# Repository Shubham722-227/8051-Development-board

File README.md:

# 8051 Development Board

## Introduction

Welcome to the 8051 Development Board! This README file will guide you through setting up and using our development board for your projects based on the 8051 microcontroller architecture.

## Board Overview

Our 8051 Development Board provides a platform for prototyping and developing applications using the popular 8051 microcontroller. It comes equipped with essential peripherals such as LEDs, push buttons, UART interface, ADC, and more, to facilitate rapid development.

## Features
- AT89S52 microcontroller
- 8 LEDs for visual feedback
- 4 push buttons for user input
- UART interface for serial communication
- ADC for analog input
- Crystal oscillator for accurate timing
- On-board voltage regulator for stable power supply
- Easily accessible headers for external connections
- Compact and durable design
## Schematic

## PCB Layout

## 3D Model

## Getting Started

1. **Hardware Setup:** Connect the 8051 Development Board to your computer using a USB cable or an external power supply. Ensure that all connections are secure and the power supply is within the recommended voltage range.
  
2. **Software Installation:** Install the necessary software tools such as an IDE (Integrated Development Environment) for 8051 microcontrollers. Popular choices include Keil uVision, SDCC (Small Device C Compiler), and Atmel Studio.
  
3. **Development Environment Configuration:** Configure your IDE to use the appropriate compiler/linker settings for the AT89S52 microcontroller. Refer to the documentation provided with your IDE for detailed instructions.
  
4. **Example Projects:** Explore the example projects included with the development board's documentation or online resources. These projects demonstrate various functionalities of the 8051 microcontroller and help you understand how to use different peripherals.
  
5. **Custom Projects:** Once you're familiar with the development board and its peripherals, start working on your custom projects. Use the provided headers to connect external components and sensors as needed. Experiment with different programming techniques to achieve your project goals.

## Resources
- **Datasheets:** Refer to the datasheets for the AT89S52 microcontroller and other components used on the development board for detailed technical information.
  
- **Tutorials:** Explore online tutorials and guides for 8051 microcontroller programming to enhance your skills and knowledge.
  
- **Community Forums:** Join online forums and communities dedicated to 8051 microcontroller development to seek help, share experiences, and collaborate with fellow enthusiasts.

## Troubleshooting
- If you encounter any issues with the development board or your projects, refer to the troubleshooting section of the documentation. Common issues such as connection problems, programming errors, and hardware malfunctions are usually addressed there.
  
- Feel free to reach out to our support team or community forums for assistance if you're unable to resolve the issue on your own.

## Feedback
We value your feedback! If you have any suggestions for improving the 8051 Development Board or its documentation, please don't hesitate to contact us. Your input helps us enhance the user experience and make our products even better.

### if you like what i do, maybe consider buying me a coffee/tea 🥺👉👈

## Authors

- [@Shubham Singh](https://github.com/Shubham722-227)

## License

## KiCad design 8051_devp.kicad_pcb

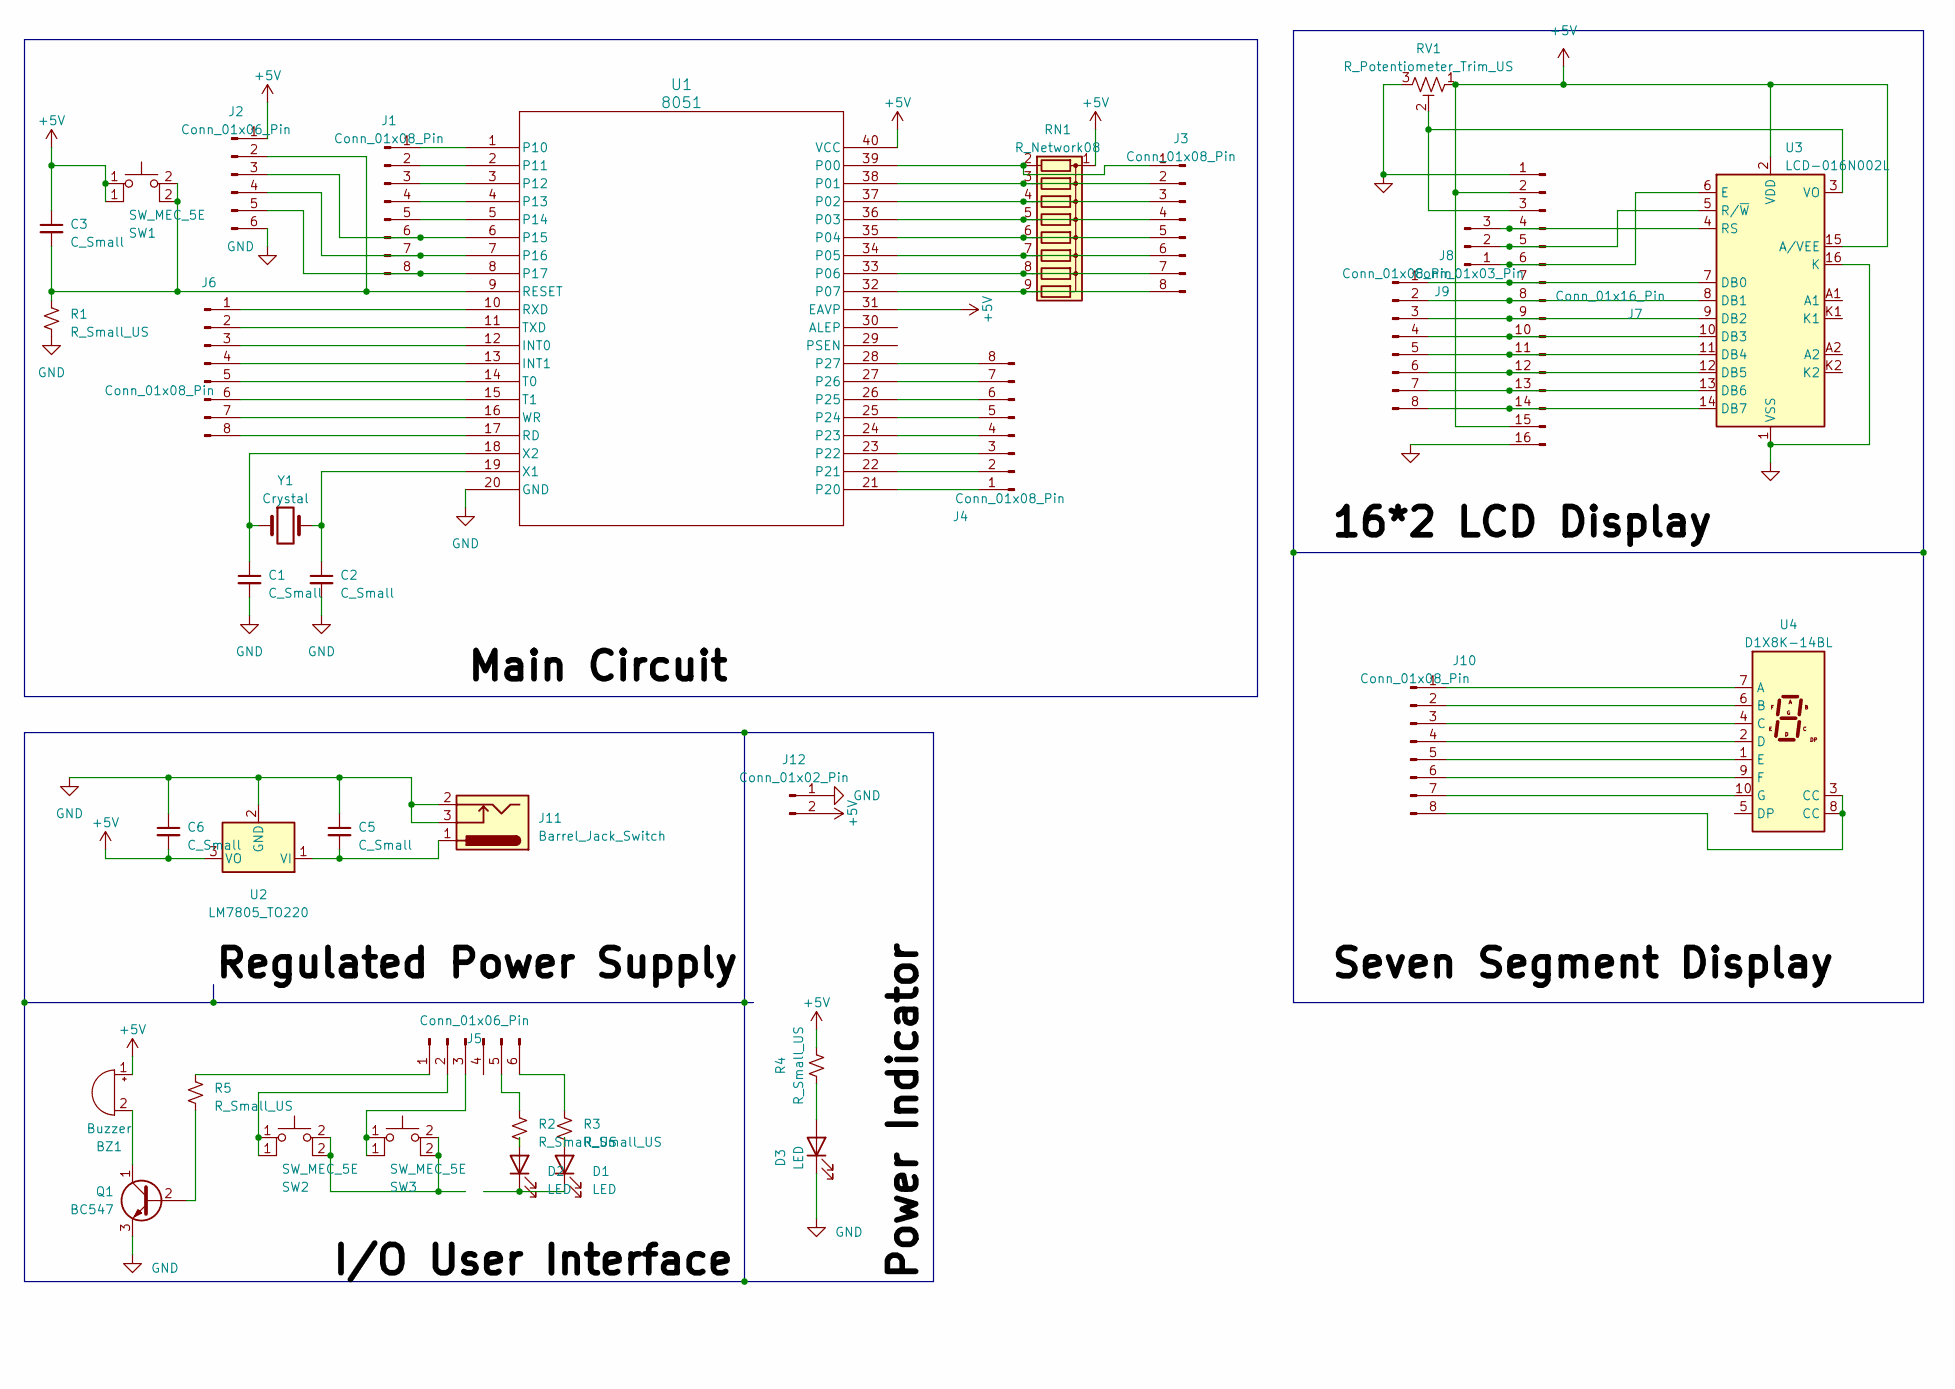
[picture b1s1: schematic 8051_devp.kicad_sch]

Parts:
BZ1: Buzzer; Buzzer_12x9.5RM7.6
C1, C2, C3, C5, C6: C_Small; C_Disc_D3.8mm_W2.6mm_P2.50mm
D1, D2, D3: LED; LED_D3.0mm_Clear
J1, J3, J4, J6, J8, J10: Conn_01x08_Pin; PinHeader_1x08_P2.54mm_Vertical
J2, J5: Conn_01x06_Pin; PinHeader_1x06_P2.54mm_Vertical
J7: Conn_01x16_Pin; PinSocket_1x16_P2.54mm_Vertical
J9: Conn_01x03_Pin; PinHeader_1x03_P2.54mm_Vertical
J11: Barrel_Jack_Switch; BarrelJack_Horizontal
J12: Conn_01x02_Pin; PinHeader_1x02_P2.54mm_Vertical
Q1: BC547; TO-92_HandSolder
R1, R2, R3, R4, R5: R_Small_US; R_Axial_DIN0207_L6.3mm_D2.5mm_P10.16mm_Horizontal
RN1: R_Network08; R_Array_SIP9
RV1: R_Potentiometer_Trim_US; Potentiometer_ACP_CA6-H2,5_Horizontal
SW1, SW2, SW3: SW_MEC_5E; SW_PUSH_6mm
U1: 8051; DIP-40_W15.24mm
U2: LM7805_TO220; TO-220-3_Vertical
U3: LCD-016N002L
U4: D1X8K-14BL; D1X8K
Y1: Crystal; Crystal_HC49-4H_Vertical

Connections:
+5V: BZ1.1 (-), C3.1, C6.2, J2.1, J7.2, J7.15, J12.2, R4.2, RN1.1 (common), RV1.1, SW1.1, U1.31 (EAVP), U1.40 (VCC), U2.3 (VO), U3.2 (VDD), U3.15 (A/VEE)
GND: C1.2, C2.2, C5.1, C6.1, D3.1 (K), J2.6, J7.1, J7.16, J11.2, J11.3, J12.1, Q1.3 (E), R1.2, RV1.3, U1.20 (GND), U2.2 (GND), U3.1 (VSS), U3.16 (K)
unnamed: BZ1.2 (+), Q1.1 (C)
unnamed: D1.2 (A), R3.2
unnamed: D1.1 (K), D2.1 (K)
unnamed: D2.2 (A), R2.2
unnamed: D3.2 (A), R4.1
unnamed: J1.1, U1.1 (P10)
unnamed: J1.2, U1.2 (P11)
unnamed: J1.3, U1.3 (P12)
unnamed: J1.4, U1.4 (P13)
unnamed: J1.5, U1.5 (P14)
unnamed: J1.6, J2.3, U1.6 (P15)
unnamed: J1.7, J2.4, U1.7 (P16)
unnamed: J1.8, J2.5, U1.8 (P17)
unnamed: C3.2, J2.2, R1.1, SW1.2 (A), U1.9 (RESET)
unnamed: J3.1, RN1.2 (R1), U1.39 (P00)
unnamed: J3.2, RN1.3 (R2), U1.38 (P01)
unnamed: J3.3, RN1.4 (R3), U1.37 (P02)
unnamed: J3.4, RN1.5 (R4), U1.36 (P03)
unnamed: J3.5, RN1.6 (R5), U1.35 (P04)
unnamed: J3.6, RN1.7 (R6), U1.34 (P05)
unnamed: J3.7, RN1.8 (R7), U1.33 (P06)
unnamed: J3.8, RN1.9 (R8), U1.32 (P07)
unnamed: J4.1, U1.21 (P20)
unnamed: J4.2, U1.22 (P21)
unnamed: J4.3, U1.23 (P22)
unnamed: J4.4, U1.24 (P23)
unnamed: J4.5, U1.25 (P24)
unnamed: J4.6, U1.26 (P25)
unnamed: J4.7, U1.27 (P26)
unnamed: J4.8, U1.28 (P27)
unnamed: J5.1, R5.1
unnamed: J5.2, SW2.1
unnamed: J5.3, SW3.1
unnamed: J5.5, R2.1
unnamed: J5.6, R3.1
unnamed: J6.1, U1.10 (RXD)
unnamed: J6.2, U1.11 (TXD)
unnamed: J6.3, U1.12 (INT0)
unnamed: J6.4, U1.13 (INT1)
unnamed: J6.5, U1.14 (T0)
unnamed: J6.6, U1.15 (T1)
unnamed: J6.7, U1.16 (WR)
unnamed: J6.8, U1.17 (RD)
unnamed: J7.3, RV1.2, U3.3 (VO)
unnamed: J7.4, J9.3, U3.4 (RS)
unnamed: J7.5, J9.2, U3.5 (R/~W)
unnamed: J7.6, J9.1, U3.6 (E)
unnamed: J7.7, J8.1, U3.7 (DB0)
unnamed: J7.8, J8.2, U3.8 (DB1)
unnamed: J7.9, J8.3, U3.9 (DB2)
unnamed: J7.10, J8.4, U3.10 (DB3)
unnamed: J7.11, J8.5, U3.11 (DB4)
unnamed: J7.12, J8.6, U3.12 (DB5)
unnamed: J7.13, J8.7, U3.13 (DB6)
unnamed: J7.14, J8.8, U3.14 (DB7)
unnamed: J10.1, U4.7 (A)
unnamed: J10.2, U4.6 (B)
unnamed: J10.3, U4.4 (C)
unnamed: J10.4, U4.2 (D)
unnamed: J10.5, U4.1 (E)
unnamed: J10.6, U4.9 (F)
unnamed: J10.7, U4.10 (G)
unnamed: J10.8, U4.3 (CC), U4.8 (CC)
unnamed: Q1.2 (B), R5.2
unnamed: SW2.2 (A), SW3.2 (A)
unnamed: C2.1, U1.19 (X1), Y1.2
unnamed: C1.1, U1.18 (X2), Y1.1
unnamed: C5.2, J11.1, U2.1 (VI)

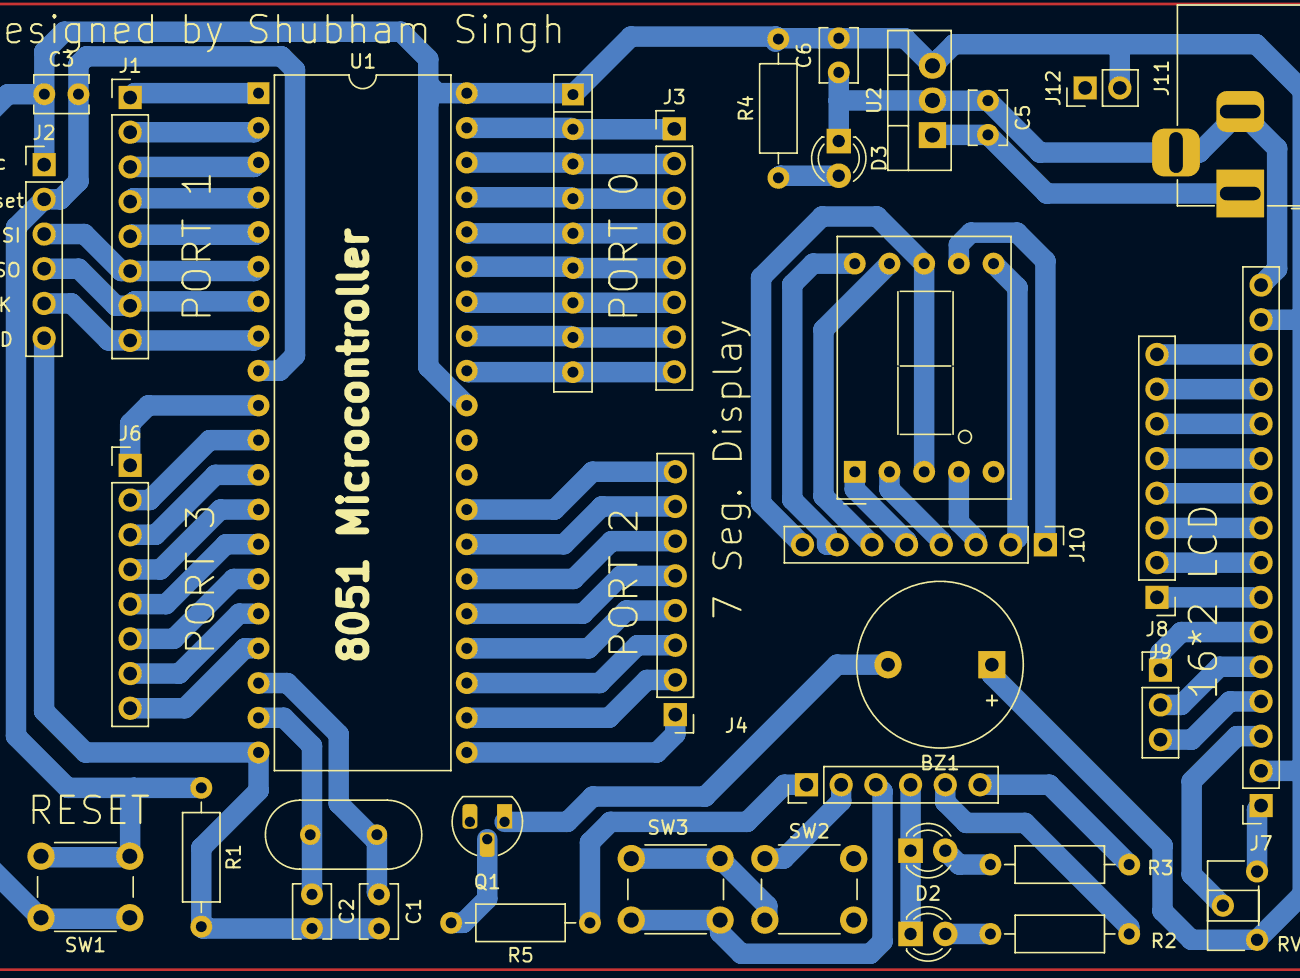
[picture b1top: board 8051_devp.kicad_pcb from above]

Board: 2 copper layers, 36 parts (0 on the bottom side), 70 nets.

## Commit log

2024-04-23 Uploaded images

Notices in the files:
README.md:
License:
[MIT License](https://choosealicense.com/licenses/mit/)
